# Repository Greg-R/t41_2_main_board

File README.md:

T41-2 Main Board Module

The documentation for this design is located here:
<https://kf5n.com/t41-2/main/>

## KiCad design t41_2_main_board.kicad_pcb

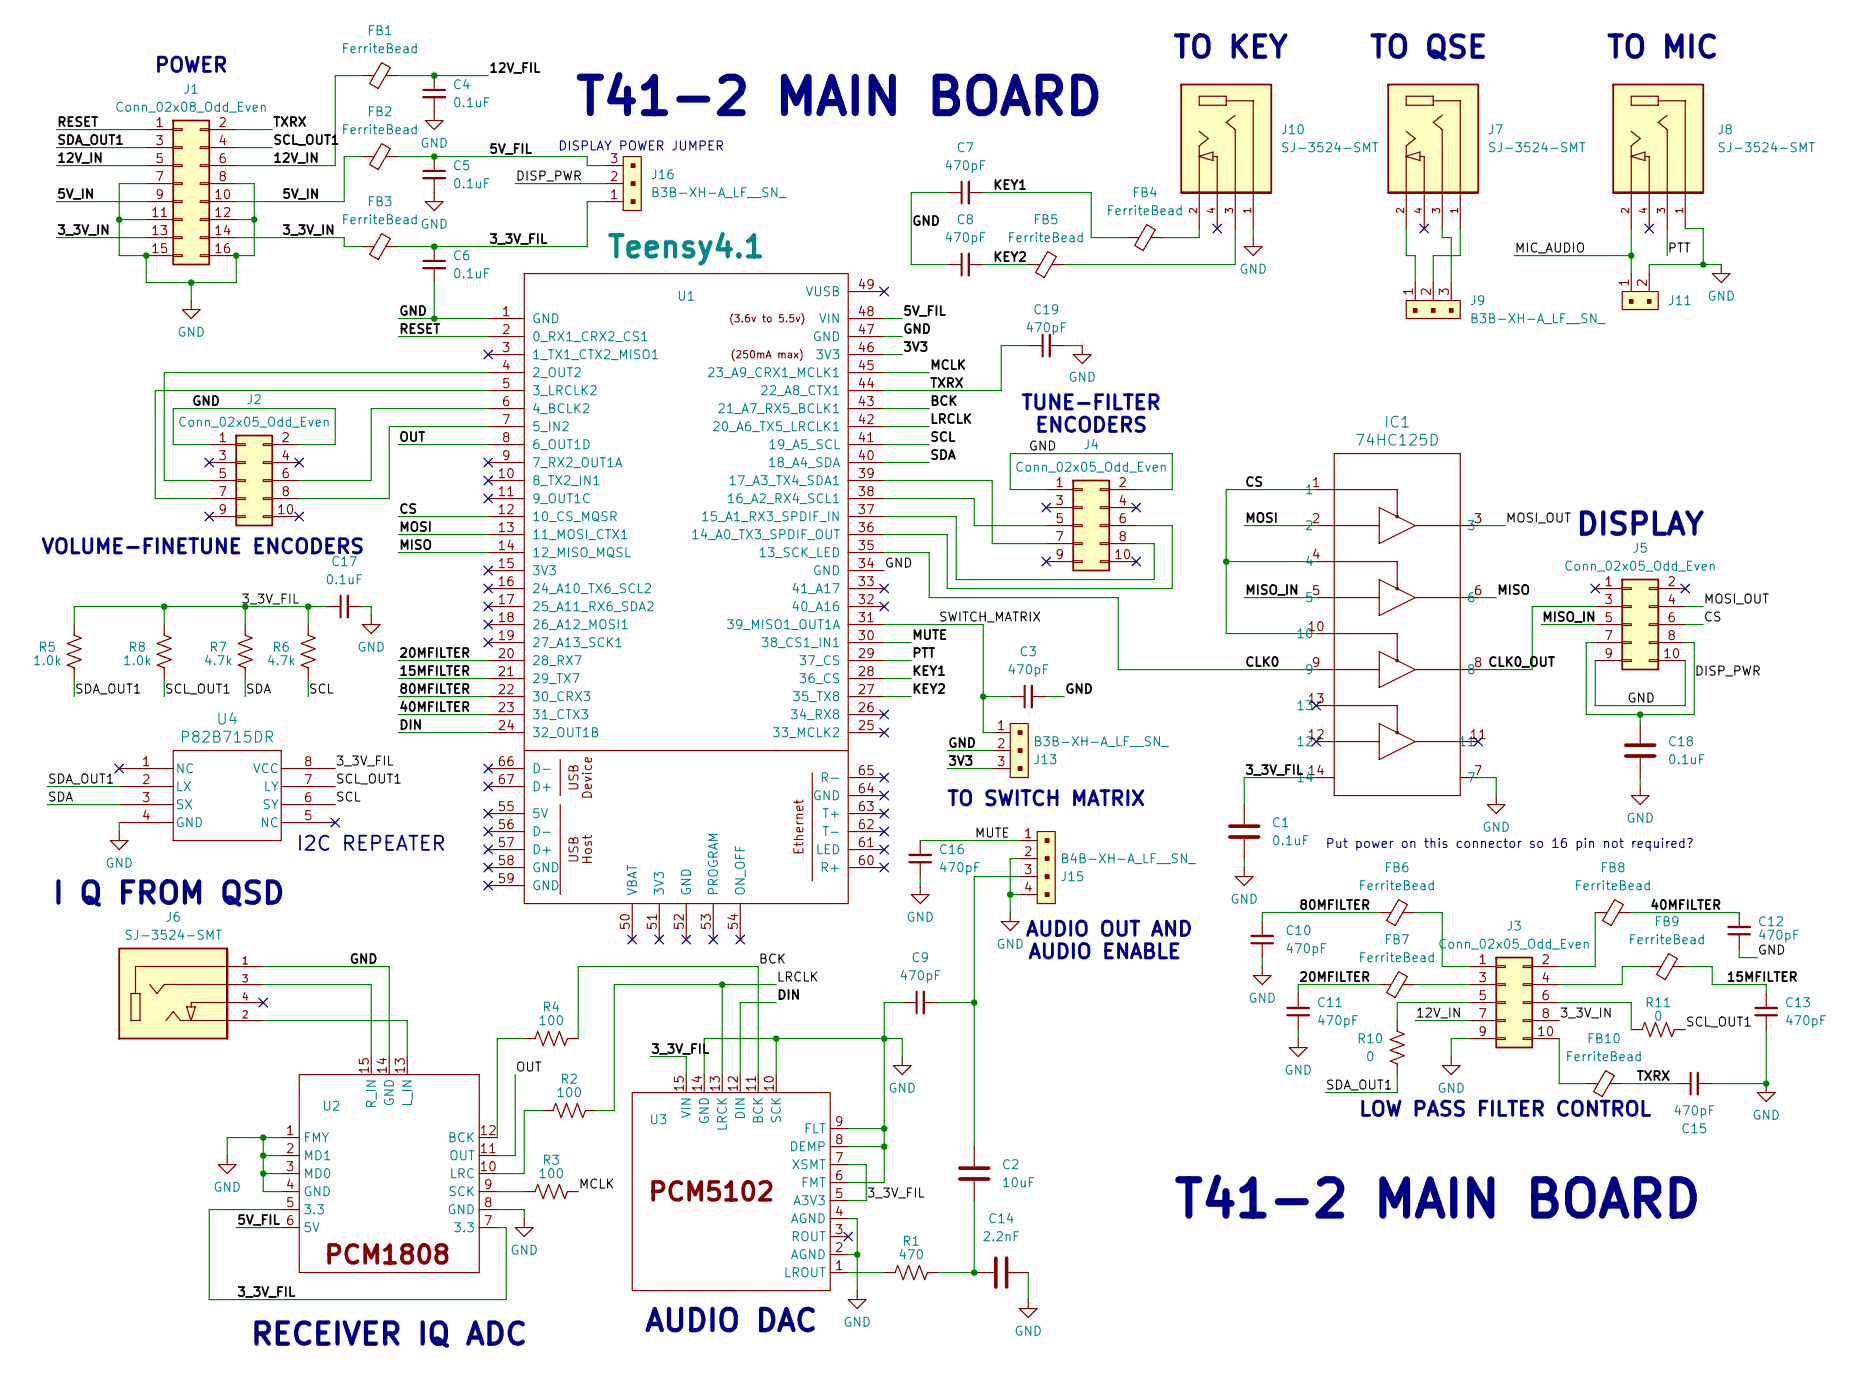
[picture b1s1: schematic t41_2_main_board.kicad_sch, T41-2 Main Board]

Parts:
C1, C4, C5, C6, C17, C18: 0.1uF; C_1206_3216Metric
C2: 10uF; C_1206_3216Metric
C3, C7, C8, C9, C10, C11, C12, C13, C15, C16, C19: 470pF; C_1206_3216Metric
C14: 2.2nF; C_1206_3216Metric
FB1, FB2, FB3, FB4, FB5, FB6, FB7, FB8, FB9, FB10: FerriteBead; L_1206_3216Metric
IC1: 74HC125D; SOIC-14_3.9x8.7mm_P1.27mm
J1: Conn_02x08_Odd_Even; IDC-Header_2x08_P2.54mm_Vertical
J2, J3, J4, J5: Conn_02x05_Odd_Even; IDC-Header_2x05_P2.54mm_Vertical
J6, J7, J8, J10: SJ-3524-SMT; CUI_SJ-3524-SMT; PARTREV 1.03
J9, J13, J16: B3B-XH-A_LF__SN_; PinHeader_1x3_P2.5mm_Drill1.1mm; MPN B3B-XH-A(LF)(SN); Digi-Key_PN 455-2248-ND
J11: B2B-XH-A_LF__SN_; PinHeader_1x2_P2.5mm_Drill1.1mm; MPN B2B-XH-A(LF)(SN); Digi-Key_PN 455-2247-ND
J15: B4B-XH-A_LF__SN_; PinHeader_1x4_P2.5mm_Drill1.1mm; MPN B4B-XH-A(LF)(SN); Digi-Key_PN 455-2249-ND
R1: 470; R_1206_3216Metric
R2, R3, R4: 100; R_1206_3216Metric
R5, R8: 1.0k; R_1206_3216Metric
R6, R7: 4.7k; R_1206_3216Metric
R10, R11: 0; R_1206_3216Metric
U1: Teensy4.1; Teensy41
U2: PCM1808_module
U3: PCM5102_module
U4: P82B715DR; SOIC-8_3.9x4.9mm_P1.27mm

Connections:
/3V3: J13.3, U1.46 (3V3)
/3_3V_FIL: C1.1, C6.1, C17.1, FB3.2, IC1.14, J16.1, R5.2, R6.2, R7.2, R8.2, U2.5 (3.3), U2.7 (3.3), U3.5 (A3V3), U3.7 (XSMT), U3.15 (VIN), U4.8 (VCC)
/3_3V_IN: FB3.1, J1.13, J1.14, J3.8
/5V_FIL: C5.1, FB2.2, J16.3, U1.48 (VIN), U2.6 (5V)
/5V_IN: FB2.1, J1.9, J1.10
/12V_FIL: C4.1, FB1.2
/12V_IN: FB1.1, J1.5, J1.6, J3.7
/15MFILTER: C13.2, FB9.2, U1.21 (29_TX7)
/20MFILTER: C11.2, FB7.1, U1.20 (28_RX7)
/40MFILTER: C12.2, FB8.2, U1.23 (31_CTX3)
/80MFILTER: C10.2, FB6.1, U1.22 (30_CRX3)
/BCK: R4.2, U1.43 (21_A7_RX5_BCLK1), U3.11 (BCK)
/CLK0: IC1.9, U1.35 (13_SCK_LED)
/CLK0_OUT: IC1.8, J5.3
/CS: IC1.1, IC1.4, IC1.10, J5.6, U1.12 (10_CS_MQSR)
/DIN: U1.24 (32_OUT1B), U3.12 (DIN)
/DISP_PWR: C18.1, J5.7, J5.8, J16.2
/KEY1: C7.2, FB4.1, U1.28 (36_CS)
/KEY2: C8.2, FB5.1, U1.27 (35_TX8)
/LRCLK: R2.2, U1.42 (20_A6_TX5_LRCLK1), U3.13 (LRCK)
/MCLK: R3.2, U1.45 (23_A9_CRX1_MCLK1)
/MIC_AUDIO: J8.2, J11.1
/MISO: IC1.6, U1.14 (12_MISO_MQSL)
/MISO_IN: IC1.5, J5.5
/MOSI: IC1.2, U1.13 (11_MOSI_CTX1)
/MOSI_OUT: IC1.3, J5.4
/MUTE: C16.2, J15.1, U1.30 (38_CS1_IN1)
/OUT: U1.8 (6_OUT1D), U2.11 (OUT)
/PTT: J8.3, U1.29 (37_CS)
/RESET: J1.1, U1.2 (0_RX1_CRX2_CS1)
/SCL: R6.1, U1.41 (19_A5_SCL), U4.6 (SY)
/SCL_OUT1: J1.4, R8.1, R11.2, U4.7 (LY)
/SDA: R7.1, U1.40 (18_A4_SDA), U4.3 (SX)
/SDA_OUT1: J1.3, R5.1, R10.1, U4.2 (LX)
/SWITCH_MATRIX: C3.1, J13.1, U1.31 (39_MISO1_OUT1A)
/TXRX: C15.1, C19.1, FB10.2, J1.2, U1.44 (22_A8_CTX1)
GND: C1.2, C3.2, C4.2, C5.2, C6.2, C7.1, C8.1, C9.1, C10.1, C11.1, C12.1, C13.1, C14.1, C15.2, C16.1, C17.2, C18.2, C19.2, IC1.7, J1.7, J1.8, J1.11, J1.12, J1.15, J1.16, J2.1, J2.2, J3.9, J4.1, J4.2, J5.9, J5.10, J6.1, J8.1, J10.1, J11.2, J13.2, J15.2, J15.4, U1.1 (GND), U1.34 (GND), U1.47 (GND), U2.1 (FMY), U2.2 (MD1), U2.3 (MD0), U2.4 (GND), U2.8 (GND), U2.14 (GND), U3.2 (AGND), U3.4 (AGND), U3.6 (FMT), U3.8 (DEMP), U3.9 (FLT), U3.10 (SCK), U3.14 (GND), U4.4 (GND)
unnamed: C2.2, C9.2, J15.3
unnamed: C2.1, C14.2, R1.2
unnamed: FB4.2, J10.2
unnamed: FB5.2, J10.3
unnamed: J2.5, U1.4 (2_OUT2)
unnamed: J2.6, U1.6 (4_BCLK2)
unnamed: J2.7, U1.5 (3_LRCLK2)
unnamed: J2.8, U1.7 (5_IN2)
unnamed: FB6.2, J3.1
unnamed: FB8.1, J3.2
unnamed: FB7.2, J3.3
unnamed: FB9.1, J3.4
unnamed: J3.5, R10.2
unnamed: J3.6, R11.1
unnamed: FB10.1, J3.10
unnamed: J4.5, U1.38 (16_A2_RX4_SCL1)
unnamed: J4.6, U1.36 (14_A0_TX3_SPDIF_OUT)
unnamed: J4.7, U1.39 (17_A3_TX4_SDA1)
unnamed: J4.8, U1.37 (15_A1_RX3_SPDIF_IN)
unnamed: J7.1, J9.2
unnamed: J7.2, J9.1
unnamed: J7.3, J9.3
unnamed: R4.1, U2.12 (BCK)
unnamed: R2.1, U2.10 (LRC)
unnamed: J6.2, U2.13 (L_IN)
unnamed: J6.3, U2.15 (R_IN)
unnamed: R3.1, U2.9 (SCK)
unnamed: R1.1, U3.1 (LROUT)

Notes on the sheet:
TO QSE
ENCODERS
TO SWITCH MATRIX
VOLUME-FINETUNE
I2C REPEATER
TO MIC
AUDIO OUT AND
I Q FROM QSD
TUNE-FILTER
DISPLAY POWER JUMPER
RECEIVER IQ ADC
DISPLAY
TO KEY
T41-2 MAIN BOARD
AUDIO ENABLE
Put power on this connector so 16 pin not required?
AUDIO DAC
POWER
LOW PASS FILTER CONTROL

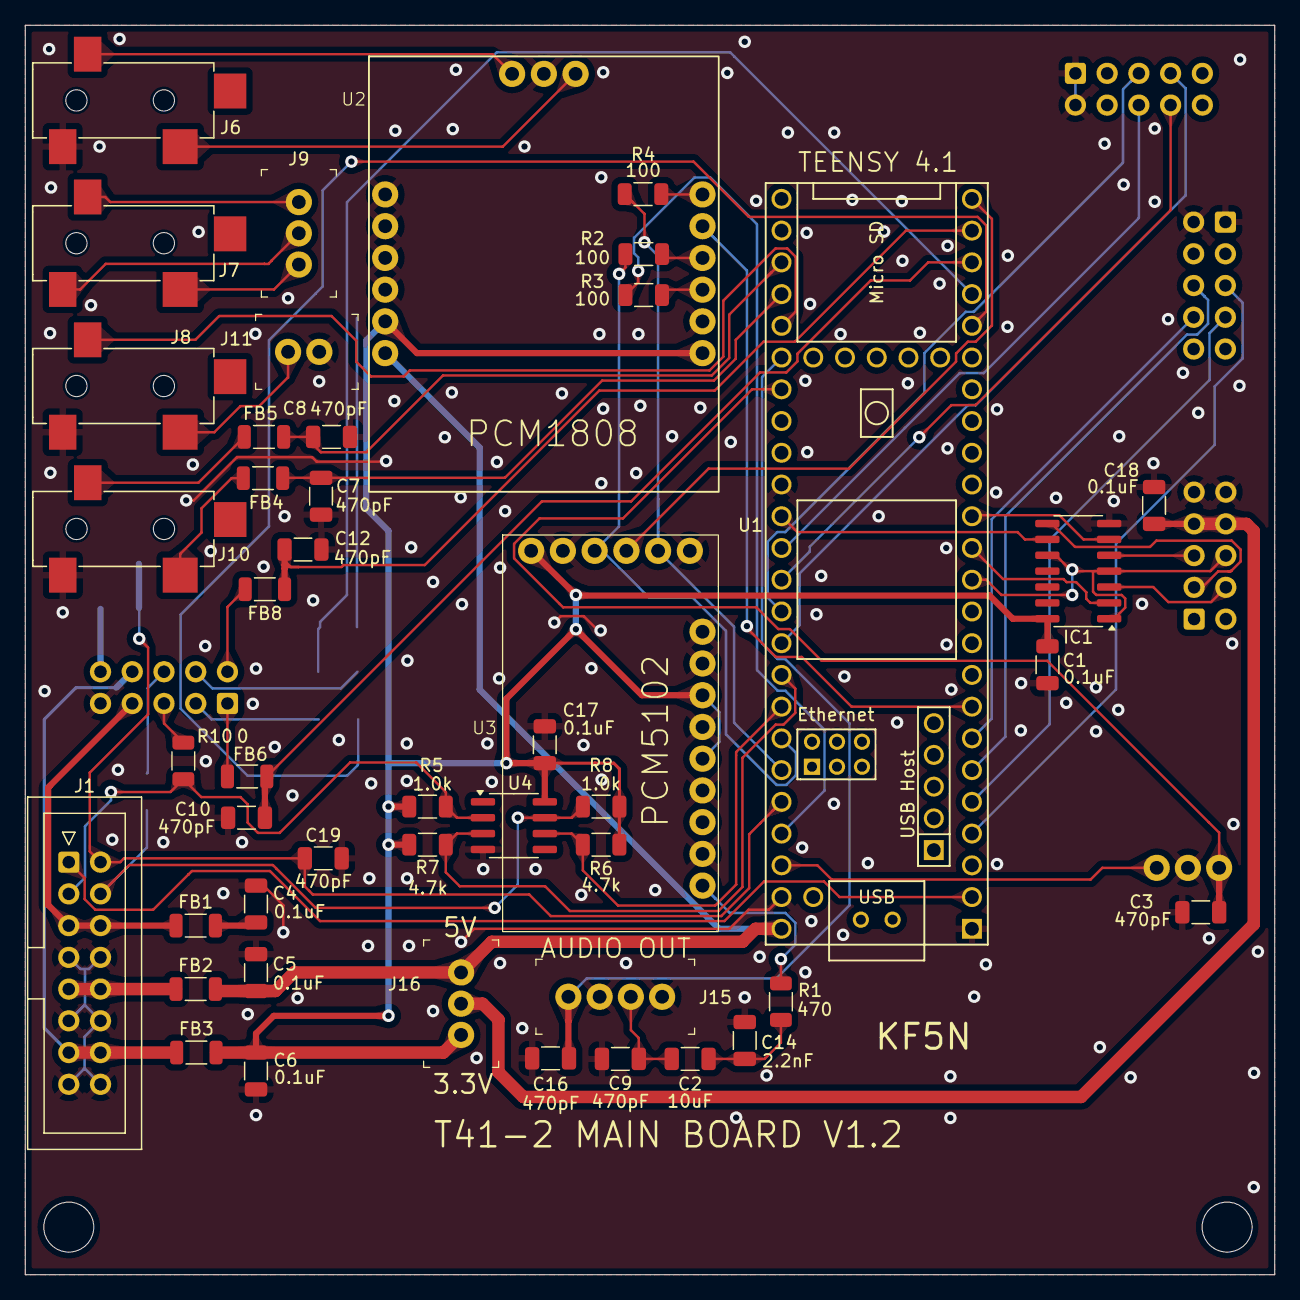
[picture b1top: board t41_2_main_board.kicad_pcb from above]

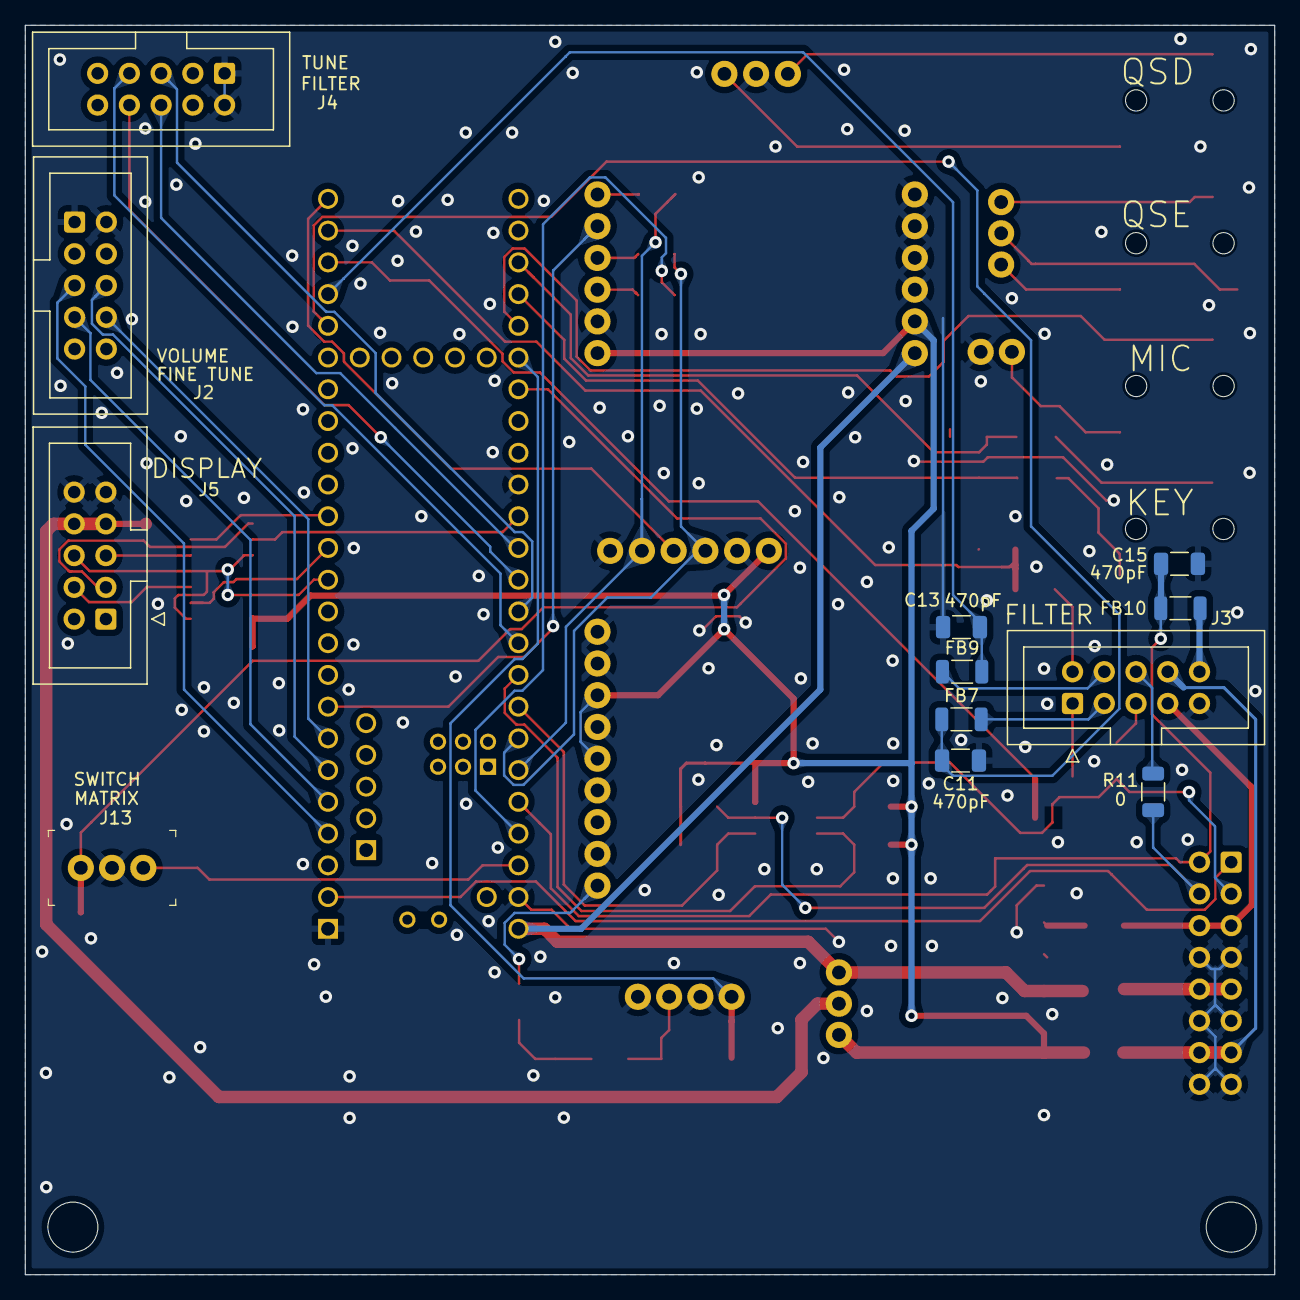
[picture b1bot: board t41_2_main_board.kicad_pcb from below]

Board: 2 copper layers, 100.0 x 100.0 mm, 58 parts (12 on the bottom side), 65 nets.

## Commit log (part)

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2024-08-25 Initial commit.
2024-08-26 Built footprints for data converters.
2024-08-28 Schematic nearing completion.
2024-08-29 Placement done.
2024-08-29 Closing in on finished layout.
2024-08-30 Branching here to alternative layout.
2024-08-31 Audio routing is not good, starting another branch.
2024-08-31 This new layout is excellent.
2024-09-01 Branching prior to adding SPDIF.
2024-09-01 To fab.
2024-09-10 V1.1 routes 0. Needs further clean-up.
2024-09-19 Fixed schematic route of 3.3 volts and 12 volts to filter connector.
2024-09-19 Layout re-do probably done.
2024-09-19 Mostly updated README.
2024-09-20 Added CERN license.
2024-09-20 Updated typo in README.
2024-09-21 Added libraries directory.
2024-09-21 Added notes for PCB symbols and footprints.
2026-02-16 Deleted backups.
